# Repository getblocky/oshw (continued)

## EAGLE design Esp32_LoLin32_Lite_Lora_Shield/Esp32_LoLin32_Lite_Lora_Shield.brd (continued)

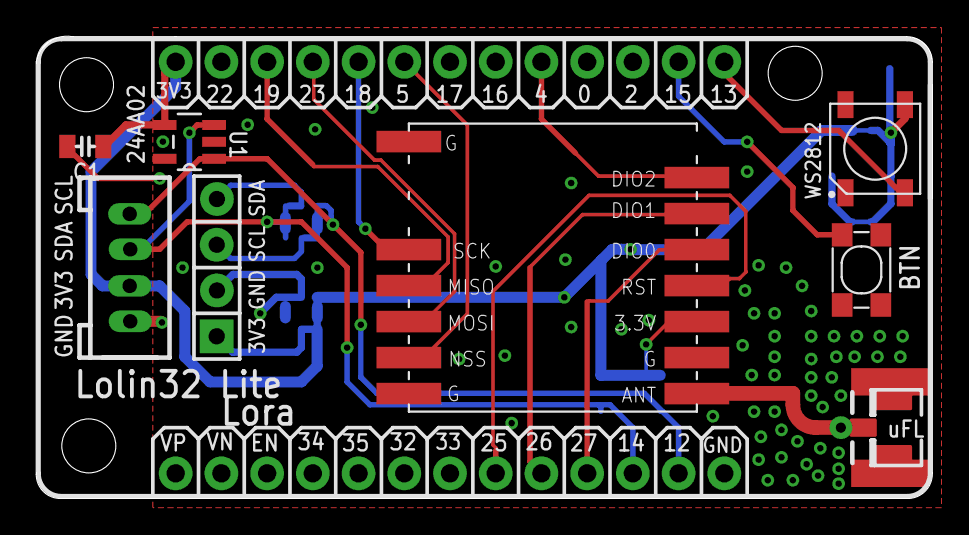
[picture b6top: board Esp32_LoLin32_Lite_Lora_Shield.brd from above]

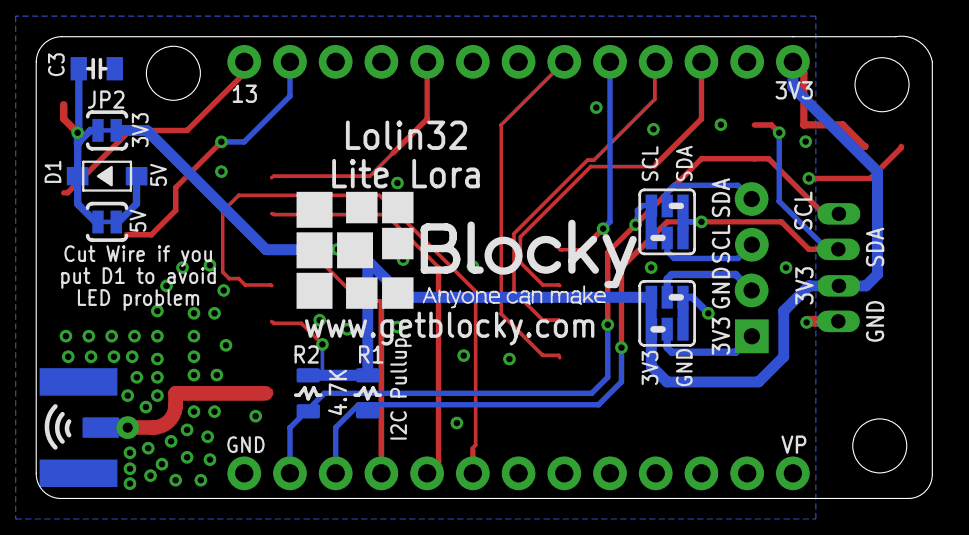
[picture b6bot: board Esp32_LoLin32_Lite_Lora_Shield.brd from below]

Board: 2 copper layers, 49.8 x 25.7 mm, 21 parts (9 on the bottom side), 21 nets.

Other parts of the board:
U$4: BLOCKY_LOGO
U$5, U$7, U$8: KFH-M3

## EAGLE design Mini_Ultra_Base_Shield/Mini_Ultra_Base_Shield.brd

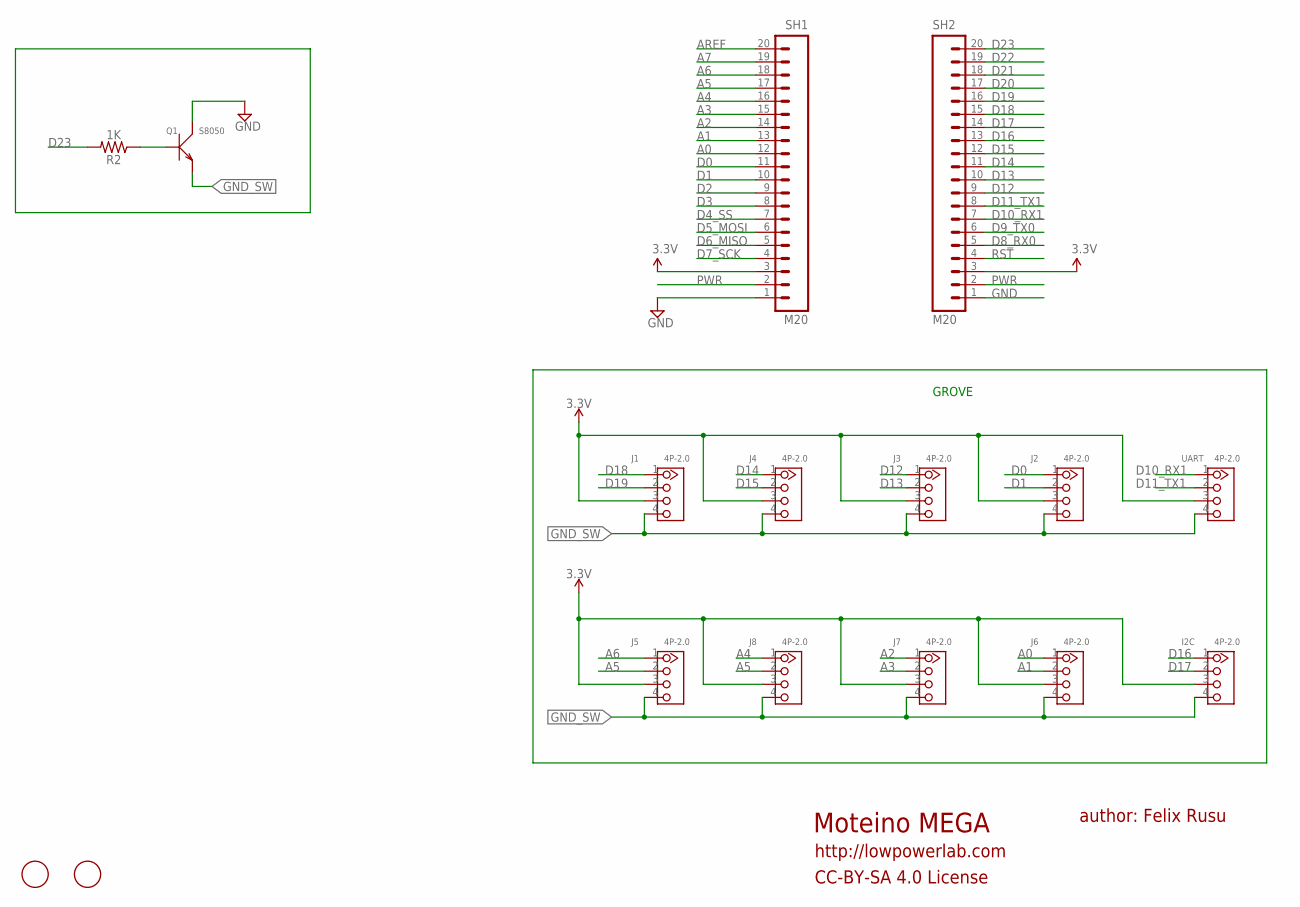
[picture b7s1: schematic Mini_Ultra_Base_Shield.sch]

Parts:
I2C: 4P-2.0; HW4-2.0
J1, J2, J3, J4, J5, J6, J7, J8: 4P-2.0; HW4-2.0
Q1: S8050; SOT-23
R2: 1K; 0603
SH1, SH2: M20; 1X20
U$2, U$7: FIDUCIAL; FIDUCIAL_1MM
UART: 4P-2.0; HW4-2.0

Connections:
A0: J6.1, SH1.12
A1: J6.2, SH1.13
A2: J7.1, SH1.14
A3: J7.2, SH1.15
A4: J8.1, SH1.16
A5: J5.2, J8.2, SH1.17
A6: J5.1, SH1.18
A7: SH1.19
AREF: SH1.20
D0: J2.1, SH1.11
D1: J2.2, SH1.10
D2: SH1.9
D3: SH1.8
D4_SS: SH1.7
D5_MOSI: SH1.6
D6_MISO: SH1.5
D7_SCK: SH1.4
D8_RX0: SH2.5
D9_TX0: SH2.6
D10_RX1: SH2.7, UART.1
D11_TX1: SH2.8, UART.2
D12: J3.1, SH2.9
D13: J3.2, SH2.10
D14: J4.1, SH2.11
D15: J4.2, SH2.12
D16: I2C.1, SH2.13
D17: I2C.2, SH2.14
D18: J1.1, SH2.15
D19: J1.2, SH2.16
D20: SH2.17
D21: SH2.18
D22: SH2.19
D23: R2.2, SH2.20
GND: Q1.3 (C), SH1.1, SH2.1
GND_SW: I2C.4, J1.4, J2.4, J3.4, J4.4, J5.4, J6.4, J7.4, J8.4, Q1.2 (E), UART.4
unnamed: Q1.1 (B), R2.1
PWR: SH1.2, SH2.2
RST: SH2.4
VCC: I2C.3, J1.3, J2.3, J3.3, J4.3, J5.3, J6.3, J7.3, J8.3, SH1.3, SH2.3, UART.3

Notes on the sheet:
Moteino MEGA
author: Felix Rusu
http://lowpowerlab.com
CC-BY-SA 4.0 License
GROVE

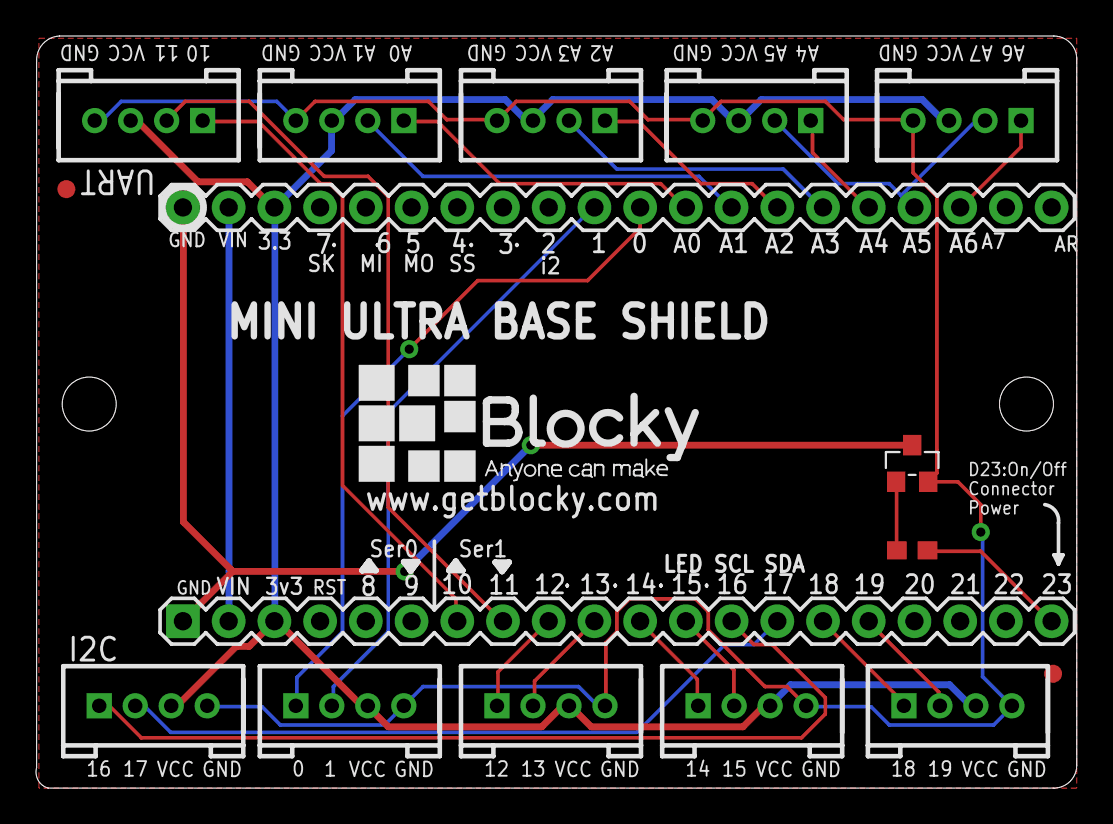
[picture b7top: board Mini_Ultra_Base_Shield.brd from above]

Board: 2 copper layers, 57.8 x 41.8 mm, 20 parts (1 on the bottom side), 25 nets.

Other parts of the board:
U$1, U$4: KFH-M3
U$3, U$5: BLOCKY_LOGO

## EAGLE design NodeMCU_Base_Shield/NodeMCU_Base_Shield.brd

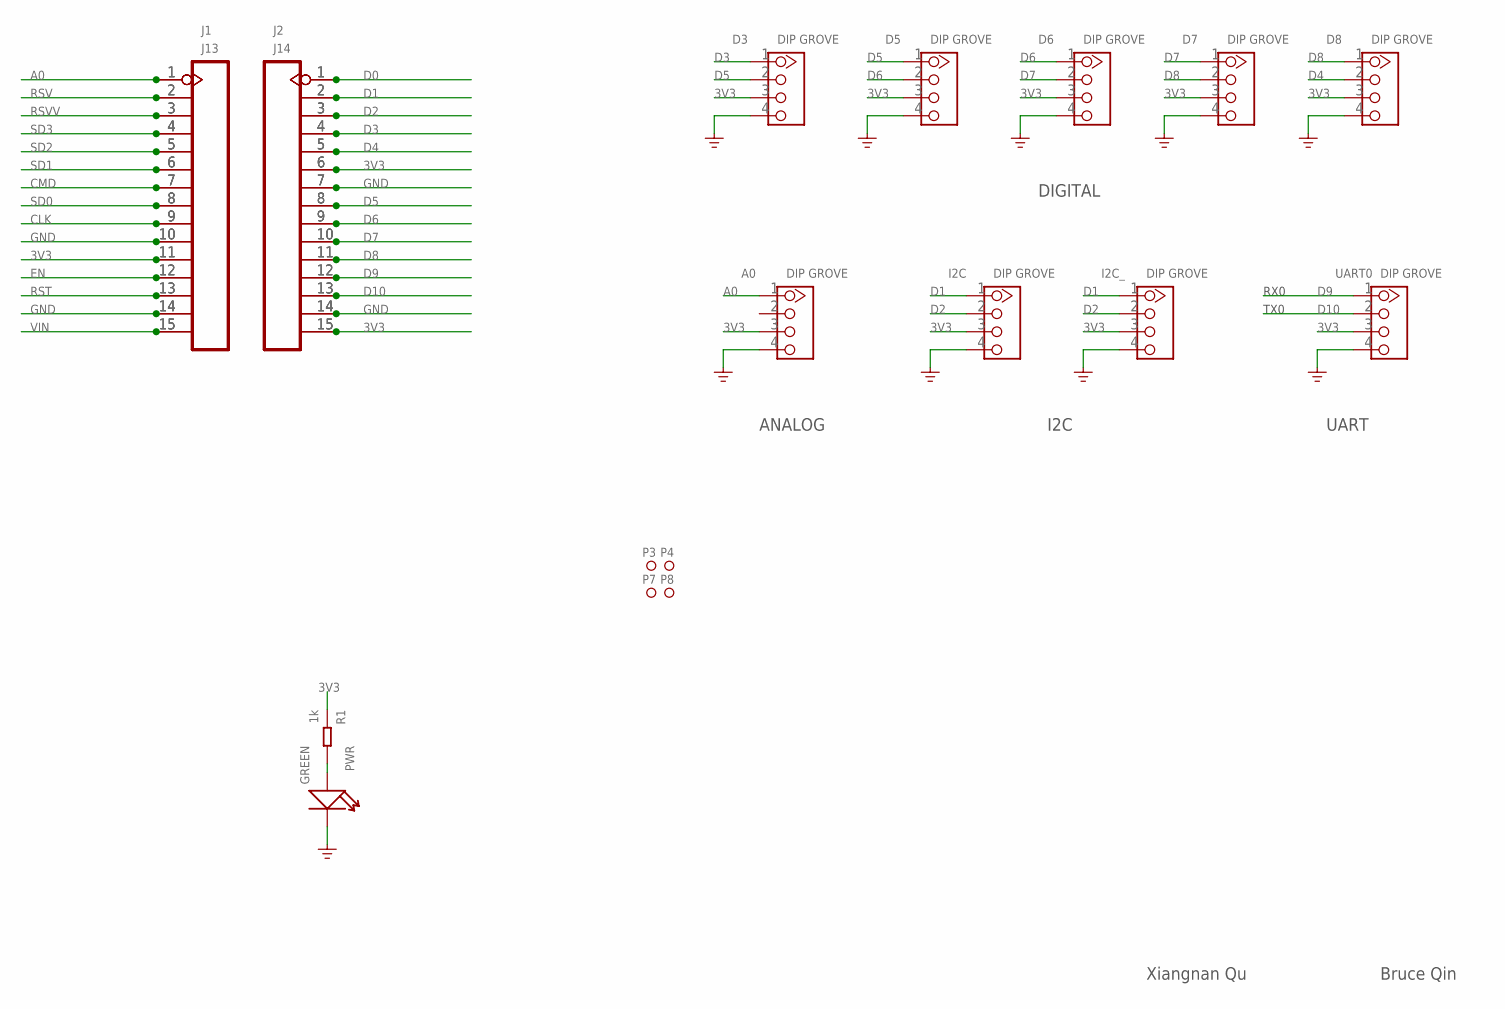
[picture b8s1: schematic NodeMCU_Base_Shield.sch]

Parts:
A0: DIP GROVE; HW4-2.0
D3, D5, D6, D7, D8: DIP GROVE; HW4-2.0
I2C, I2C_: DIP GROVE; HW4-2.0
J1, J2, J13, J14: HEADER-15P'2.54'; H15-2.54
P3, P4, P7, P8: MARK-1.0'ANNULAR'; ROUND-MARK-1.0
PWR: GREEN; LED-0603
R1: 1k; R0603
UART0: DIP GROVE; HW4-2.0

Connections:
3V3: A0.3, D3.3, D5.3, D6.3, D7.3, D8.3, I2C.3, I2C_.3, J1.11, J2.6, J2.15, J13.11, J14.6, J14.15, R1.1, UART0.3
A0: A0.1, J1.1, J13.1
CLK: J1.9, J13.9
CMD: J1.7, J13.7
D0: J2.1, J14.1
D1: I2C.1, I2C_.1, J2.2, J14.2
D2: I2C.2, I2C_.2, J2.3, J14.3
D3: D3.1, J2.4, J14.4
D4: D8.2, J2.5, J14.5
D5: D3.2, D5.1, J2.8, J14.8
D6: D5.2, D6.1, J2.9, J14.9
D7: D6.2, D7.1, J2.10, J14.10
D8: D7.2, D8.1, J2.11, J14.11
D9: J2.12, J14.12, UART0.1
D10: J2.13, J14.13, UART0.2
EN: J1.12, J13.12
GND: A0.4, D3.4, D5.4, D6.4, D7.4, D8.4, I2C.4, I2C_.4, J1.10, J1.14, J2.7, J2.14, J13.10, J13.14, J14.7, J14.14, PWR.-, UART0.4
unnamed: PWR.+, R1.2
RST: J1.13, J13.13
RSV: J1.2, J13.2
RSVV: J1.3, J13.3
SD0: J1.8, J13.8
SD1: J1.6, J13.6
SD2: J1.5, J13.5
SD3: J1.4, J13.4
VIN: J1.15, J13.15

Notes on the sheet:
Xiangnan Qu
Bruce Qin
UART
TX0
RX0
I2C
ANALOG
DIGITAL

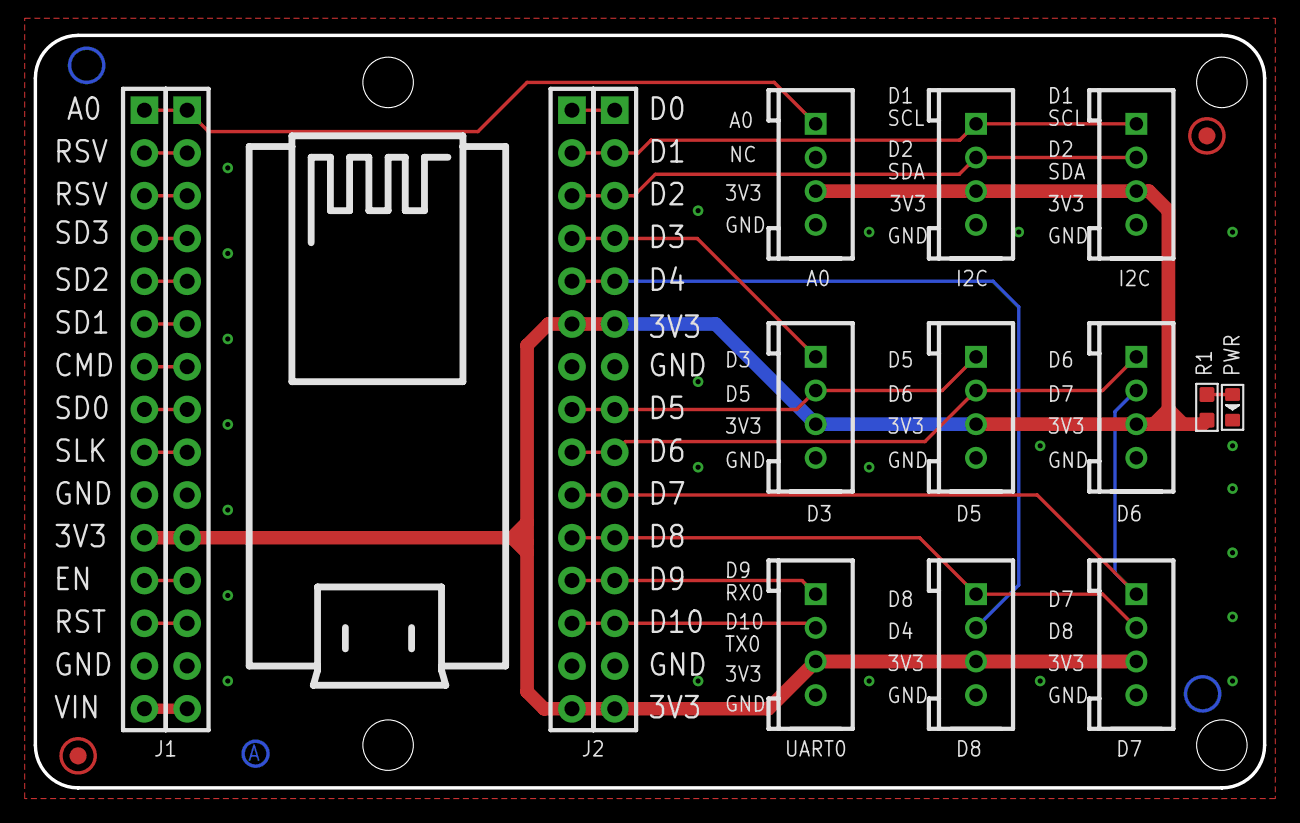
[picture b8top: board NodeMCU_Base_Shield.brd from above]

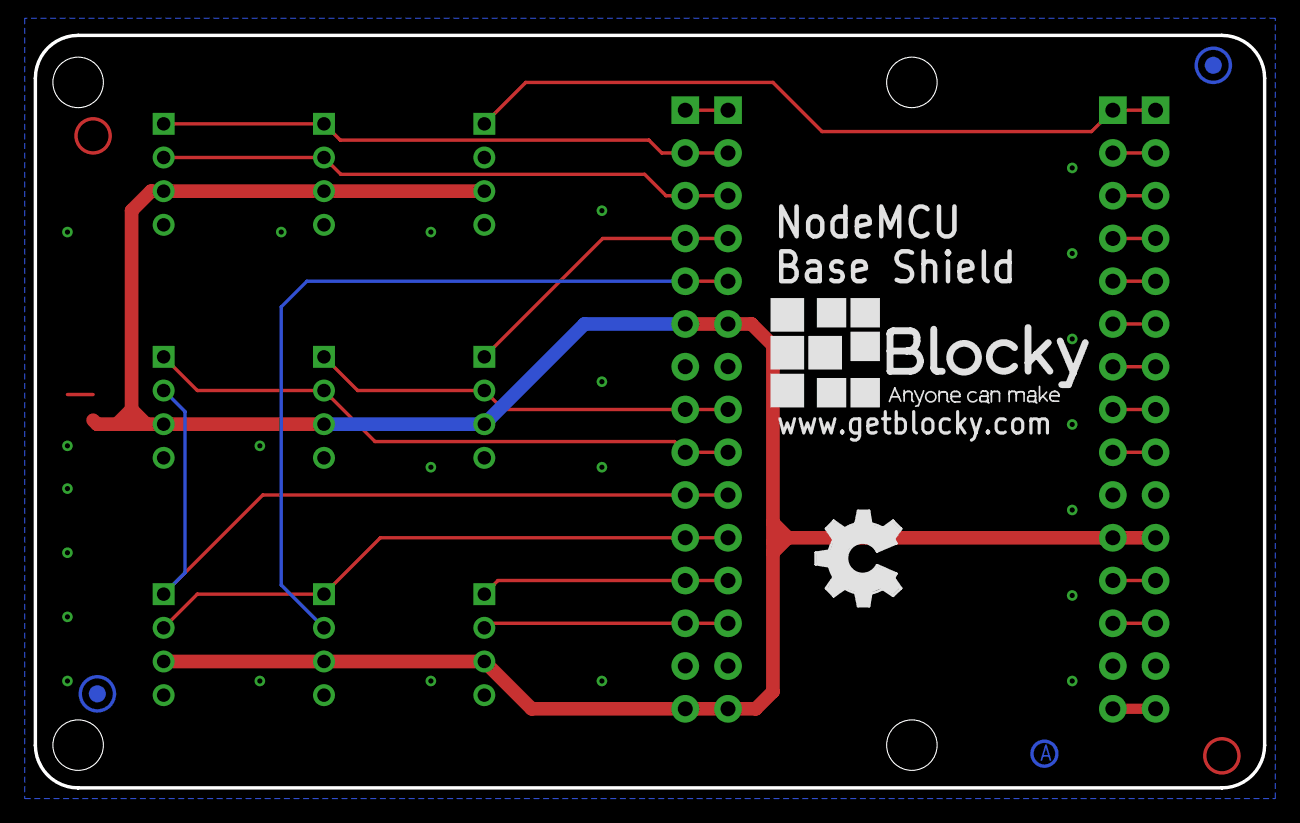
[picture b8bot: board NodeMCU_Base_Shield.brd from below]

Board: 2 copper layers, 73.0 x 44.7 mm, 21 parts (4 on the bottom side), 26 nets.

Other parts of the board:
U$7: BLOCKY_LOGO
U$27: OSHW_FILLX200_NOTEXT
